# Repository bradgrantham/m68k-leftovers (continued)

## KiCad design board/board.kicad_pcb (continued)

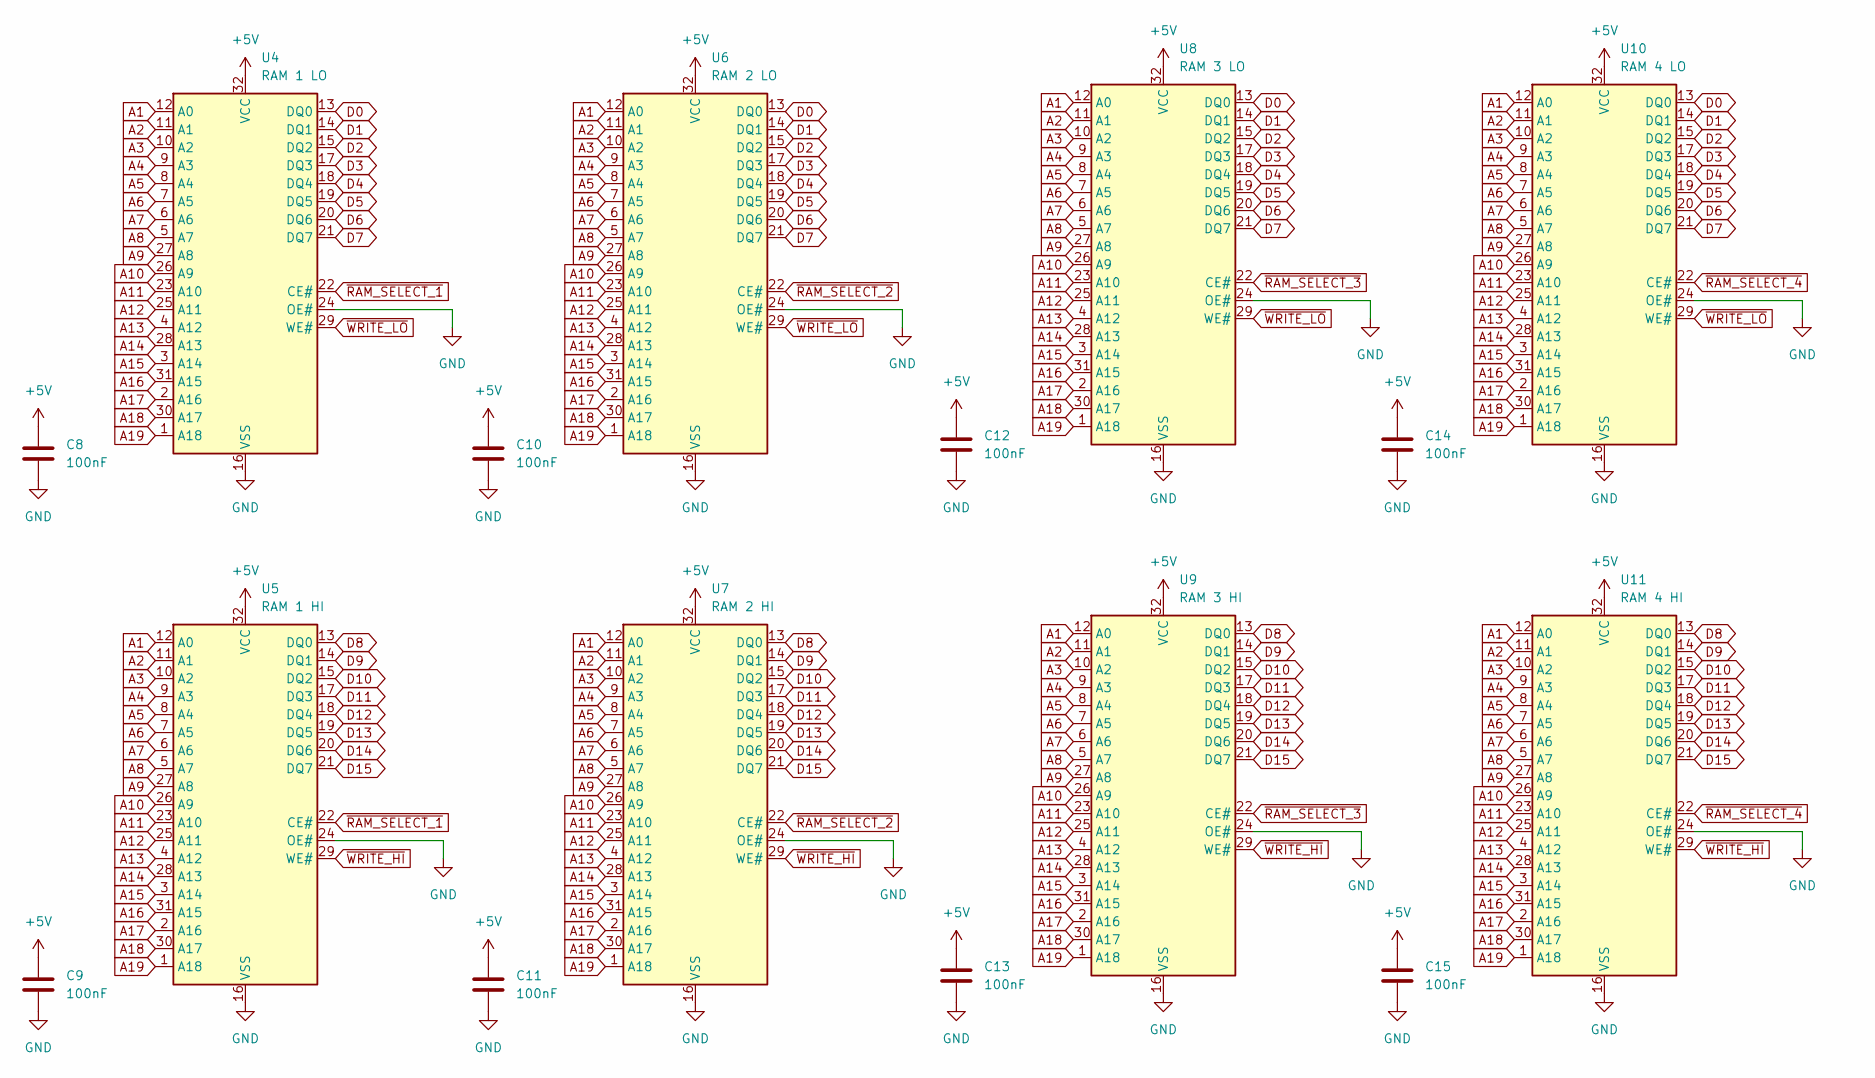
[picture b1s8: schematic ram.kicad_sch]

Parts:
C8, C9, C10, C11, C12, C13, C14, C15: 100nF; C_Disc_D5.0mm_W2.5mm_P5.00mm
U4: RAM 1 LO; DIP-32_W15.24mm
U5: RAM 1 HI; DIP-32_W15.24mm
U6: RAM 2 LO; DIP-32_W15.24mm
U7: RAM 2 HI; DIP-32_W15.24mm
U8: RAM 3 LO; DIP-32_W15.24mm
U9: RAM 3 HI; DIP-32_W15.24mm
U10: RAM 4 LO; DIP-32_W15.24mm
U11: RAM 4 HI; DIP-32_W15.24mm

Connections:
+5V: C8.1, C9.1, C10.1, C11.1, C12.1, C13.1, C14.1, C15.1, U4.32 (VCC), U5.32 (VCC), U6.32 (VCC), U7.32 (VCC), U8.32 (VCC), U9.32 (VCC), U10.32 (VCC), U11.32 (VCC); also elsewhere on the board
A1: U4.12 (A0), U5.12 (A0), U6.12 (A0), U7.12 (A0), U8.12 (A0), U9.12 (A0), U10.12 (A0), U11.12 (A0); also elsewhere on the board
A2: U4.11 (A1), U5.11 (A1), U6.11 (A1), U7.11 (A1), U8.11 (A1), U9.11 (A1), U10.11 (A1), U11.11 (A1); also elsewhere on the board
A3: U4.10 (A2), U5.10 (A2), U6.10 (A2), U7.10 (A2), U8.10 (A2), U9.10 (A2), U10.10 (A2), U11.10 (A2); also elsewhere on the board
A4: U4.9 (A3), U5.9 (A3), U6.9 (A3), U7.9 (A3), U8.9 (A3), U9.9 (A3), U10.9 (A3), U11.9 (A3); also elsewhere on the board
A5: U4.8 (A4), U5.8 (A4), U6.8 (A4), U7.8 (A4), U8.8 (A4), U9.8 (A4), U10.8 (A4), U11.8 (A4); also elsewhere on the board
A6: U4.7 (A5), U5.7 (A5), U6.7 (A5), U7.7 (A5), U8.7 (A5), U9.7 (A5), U10.7 (A5), U11.7 (A5); also elsewhere on the board
A7: U4.6 (A6), U5.6 (A6), U6.6 (A6), U7.6 (A6), U8.6 (A6), U9.6 (A6), U10.6 (A6), U11.6 (A6); also elsewhere on the board
A8: U4.5 (A7), U5.5 (A7), U6.5 (A7), U7.5 (A7), U8.5 (A7), U9.5 (A7), U10.5 (A7), U11.5 (A7); also elsewhere on the board
A9: U4.27 (A8), U5.27 (A8), U6.27 (A8), U7.27 (A8), U8.27 (A8), U9.27 (A8), U10.27 (A8), U11.27 (A8); also elsewhere on the board
A10: U4.26 (A9), U5.26 (A9), U6.26 (A9), U7.26 (A9), U8.26 (A9), U9.26 (A9), U10.26 (A9), U11.26 (A9); also elsewhere on the board
A11: U4.23 (A10), U5.23 (A10), U6.23 (A10), U7.23 (A10), U8.23 (A10), U9.23 (A10), U10.23 (A10), U11.23 (A10); also elsewhere on the board
A12: U4.25 (A11), U5.25 (A11), U6.25 (A11), U7.25 (A11), U8.25 (A11), U9.25 (A11), U10.25 (A11), U11.25 (A11); also elsewhere on the board
A13: U4.4 (A12), U5.4 (A12), U6.4 (A12), U7.4 (A12), U8.4 (A12), U9.4 (A12), U10.4 (A12), U11.4 (A12); also elsewhere on the board
A14: U4.28 (A13), U5.28 (A13), U6.28 (A13), U7.28 (A13), U8.28 (A13), U9.28 (A13), U10.28 (A13), U11.28 (A13); also elsewhere on the board
A15: U4.3 (A14), U5.3 (A14), U6.3 (A14), U7.3 (A14), U8.3 (A14), U9.3 (A14), U10.3 (A14), U11.3 (A14); also elsewhere on the board
A16: U4.31 (A15), U5.31 (A15), U6.31 (A15), U7.31 (A15), U8.31 (A15), U9.31 (A15), U10.31 (A15), U11.31 (A15); also elsewhere on the board
A17: U4.2 (A16), U5.2 (A16), U6.2 (A16), U7.2 (A16), U8.2 (A16), U9.2 (A16), U10.2 (A16), U11.2 (A16); also elsewhere on the board
A18: U4.30 (A17), U5.30 (A17), U6.30 (A17), U7.30 (A17), U8.30 (A17), U9.30 (A17), U10.30 (A17), U11.30 (A17); also elsewhere on the board
A19: U4.1 (A18), U5.1 (A18), U6.1 (A18), U7.1 (A18), U8.1 (A18), U9.1 (A18), U10.1 (A18), U11.1 (A18); also elsewhere on the board
D0: U4.13 (DQ0), U6.13 (DQ0), U8.13 (DQ0), U10.13 (DQ0); also elsewhere on the board
D1: U4.14 (DQ1), U6.14 (DQ1), U8.14 (DQ1), U10.14 (DQ1); also elsewhere on the board
D2: U4.15 (DQ2), U6.15 (DQ2), U8.15 (DQ2), U10.15 (DQ2); also elsewhere on the board
D3: U4.17 (DQ3), U6.17 (DQ3), U8.17 (DQ3), U10.17 (DQ3); also elsewhere on the board
D4: U4.18 (DQ4), U6.18 (DQ4), U8.18 (DQ4), U10.18 (DQ4); also elsewhere on the board
D5: U4.19 (DQ5), U6.19 (DQ5), U8.19 (DQ5), U10.19 (DQ5); also elsewhere on the board
D6: U4.20 (DQ6), U6.20 (DQ6), U8.20 (DQ6), U10.20 (DQ6); also elsewhere on the board
D7: U4.21 (DQ7), U6.21 (DQ7), U8.21 (DQ7), U10.21 (DQ7); also elsewhere on the board
D8: U5.13 (DQ0), U7.13 (DQ0), U9.13 (DQ0), U11.13 (DQ0); also elsewhere on the board
D9: U5.14 (DQ1), U7.14 (DQ1), U9.14 (DQ1), U11.14 (DQ1); also elsewhere on the board
D10: U5.15 (DQ2), U7.15 (DQ2), U9.15 (DQ2), U11.15 (DQ2); also elsewhere on the board
D11: U5.17 (DQ3), U7.17 (DQ3), U9.17 (DQ3), U11.17 (DQ3); also elsewhere on the board
D12: U5.18 (DQ4), U7.18 (DQ4), U9.18 (DQ4), U11.18 (DQ4); also elsewhere on the board
D13: U5.19 (DQ5), U7.19 (DQ5), U9.19 (DQ5), U11.19 (DQ5); also elsewhere on the board
D14: U5.20 (DQ6), U7.20 (DQ6), U9.20 (DQ6), U11.20 (DQ6); also elsewhere on the board
D15: U5.21 (DQ7), U7.21 (DQ7), U9.21 (DQ7), U11.21 (DQ7); also elsewhere on the board
GND: C8.2, C9.2, C10.2, C11.2, C12.2, C13.2, C14.2, C15.2, U4.16 (VSS), U4.24 (OE#), U5.16 (VSS), U5.24 (OE#), U6.16 (VSS), U6.24 (OE#), U7.16 (VSS), U7.24 (OE#), U8.16 (VSS), U8.24 (OE#), U9.16 (VSS), U9.24 (OE#), U10.16 (VSS), U10.24 (OE#), U11.16 (VSS), U11.24 (OE#); also elsewhere on the board
~RAM_SELECT_1: U4.22 (CE#), U5.22 (CE#); also elsewhere on the board
~RAM_SELECT_2: U6.22 (CE#), U7.22 (CE#); also elsewhere on the board
~RAM_SELECT_3: U8.22 (CE#), U9.22 (CE#); also elsewhere on the board
~RAM_SELECT_4: U10.22 (CE#), U11.22 (CE#); also elsewhere on the board
~WRITE_HI: U5.29 (WE#), U7.29 (WE#), U9.29 (WE#), U11.29 (WE#); also elsewhere on the board
~WRITE_LO: U4.29 (WE#), U6.29 (WE#), U8.29 (WE#), U10.29 (WE#); also elsewhere on the board

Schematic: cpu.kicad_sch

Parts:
C4, C5: 100nF; C_Disc_D5.0mm_W2.5mm_P5.00mm
R3, R4, R6: 100K; R_Axial_DIN0207_L6.3mm_D2.5mm_P10.16mm_Horizontal
R13, R34, R54, R55: 10K; R_Axial_DIN0207_L6.3mm_D2.5mm_P10.16mm_Horizontal
U1: MC68000P; DIP-64_W22.86mm

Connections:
+5V: C4.1, C5.1, R3.1, R4.1, R6.1, R13.1, R34.1, R54.1, R55.1, U1.14 (V_{CC}), U1.49 (V_{CC}); also elsewhere on the board
A1: U1.29 (A1); also elsewhere on the board
A2: U1.30 (A2); also elsewhere on the board
A3: U1.31 (A3); also elsewhere on the board
A4: U1.32 (A4); also elsewhere on the board
A5: U1.33 (A5); also elsewhere on the board
A6: U1.34 (A6); also elsewhere on the board
A7: U1.35 (A7); also elsewhere on the board
A8: U1.36 (A8); also elsewhere on the board
A9: U1.37 (A9); also elsewhere on the board
A10: U1.38 (A10); also elsewhere on the board
A11: U1.39 (A11); also elsewhere on the board
A12: U1.40 (A12); also elsewhere on the board
A13: U1.41 (A13); also elsewhere on the board
A14: U1.42 (A14); also elsewhere on the board
A15: U1.43 (A15); also elsewhere on the board
A16: U1.44 (A16); also elsewhere on the board
A17: U1.45 (A17); also elsewhere on the board
A18: U1.46 (A18); also elsewhere on the board
A19: U1.47 (A19); also elsewhere on the board
A20: U1.48 (A20); also elsewhere on the board
A21: U1.50 (A21); also elsewhere on the board
A22: U1.51 (A22); also elsewhere on the board
A23: U1.52 (A23); also elsewhere on the board
CPUCLK: U1.15 (CLK); also elsewhere on the board
D0: U1.5 (D0); also elsewhere on the board
D1: U1.4 (D1); also elsewhere on the board
D2: U1.3 (D2); also elsewhere on the board
D3: U1.2 (D3); also elsewhere on the board
D4: U1.1 (D4); also elsewhere on the board
D5: U1.64 (D5); also elsewhere on the board
D6: U1.63 (D6); also elsewhere on the board
D7: U1.62 (D7); also elsewhere on the board
D8: U1.61 (D8); also elsewhere on the board
D9: U1.60 (D9); also elsewhere on the board
D10: U1.59 (D10); also elsewhere on the board
D11: U1.58 (D11); also elsewhere on the board
D12: U1.57 (D12); also elsewhere on the board
D13: U1.56 (D13); also elsewhere on the board
D14: U1.55 (D14); also elsewhere on the board
D15: U1.54 (D15); also elsewhere on the board
FC0: U1.28 (FC0); also elsewhere on the board
FC1: U1.27 (FC1); also elsewhere on the board
FC2: U1.26 (FC2); also elsewhere on the board
GND: C4.2, C5.2, U1.16 (GND), U1.53 (GND); also elsewhere on the board
unnamed: R6.2, U1.21 (~VPA)
R/~W: U1.9 (R/~W); also elsewhere on the board
~AS: U1.6 (~AS); also elsewhere on the board
~BERR: U1.22 (~BERR); also elsewhere on the board
~BGACK: R4.2, U1.12 (~BGACK); also elsewhere on the board
~BG: U1.11 (~BG); also elsewhere on the board
~BR: R3.2, U1.13 (~BR); also elsewhere on the board
~DTACK: U1.10 (~DTACK); also elsewhere on the board
~HALT: R54.2, U1.17 (~HALT); also elsewhere on the board
~IPL0: R13.2, U1.25 (~IPL0); also elsewhere on the board
~IPL1: R34.2, U1.24 (~IPL1); also elsewhere on the board
~IPL2: R55.2, U1.23 (~IPL2); also elsewhere on the board
~LDS: U1.8 (~LDS); also elsewhere on the board
~RESET: U1.18 (~RESET); also elsewhere on the board
~UDS: U1.7 (~UDS); also elsewhere on the board

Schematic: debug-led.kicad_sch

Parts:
C24, C36: 100nF; C_Disc_D5.0mm_W2.5mm_P5.00mm
C25: 10nF; C_Disc_D3.0mm_W1.6mm_P2.50mm
C26: 100µF; CP_Radial_D5.0mm_P2.50mm
J7: STEREO_OUT; SAMESKY_SJ3-35063B; PARTREV 1.0
LS1: Speaker; MagneticBuzzer_StarMicronics_QMX
R52, R53: 1K; R_Axial_DIN0207_L6.3mm_D2.5mm_P10.16mm_Horizontal
R57, R58: 100; R_Axial_DIN0207_L6.3mm_D2.5mm_P10.16mm_Horizontal
R59: 47; R_Axial_DIN0207_L6.3mm_D2.5mm_P10.16mm_Horizontal
R60: 4610X-R2R-103LF; BO_4610X
U15: LM358; DIP-8_W7.62mm
U23: 74HC373; DIP-20_W7.62mm

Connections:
+5V: C24.1, C36.1, U15.8 (V+), U23.20 (VCC); also elsewhere on the board
AUDIO0: R60.9, U23.2 (O0)
AUDIO1: R60.8, U23.5 (O1)
AUDIO2: R60.7, U23.6 (O2)
AUDIO3: R60.6, U23.9 (O3)
AUDIO4: R60.5, U23.12 (O4)
AUDIO5: R60.4, U23.15 (O5)
AUDIO6: R60.3, U23.16 (O6)
AUDIO7: R60.2, U23.19 (O7)
AUDIO_LE: U23.11 (LE); also elsewhere on the board
D0: U23.3 (D0); also elsewhere on the board
D1: U23.4 (D1); also elsewhere on the board
D2: U23.7 (D2); also elsewhere on the board
D3: U23.8 (D3); also elsewhere on the board
D4: U23.13 (D4); also elsewhere on the board
D5: U23.14 (D5); also elsewhere on the board
D6: U23.17 (D6); also elsewhere on the board
D7: U23.18 (D7); also elsewhere on the board
GND: C24.2, C25.2, C36.2, J7.1, LS1.2, R53.1, R60.10, U15.4 (V-), U15.5 (+), U23.1 (OE), U23.10 (GND); also elsewhere on the board
unnamed: C25.1, C26.1, R52.2
unnamed: C26.2, R53.2, R57.2, R58.2
unnamed: J7.2, R57.1
unnamed: J7.3, R58.1
unnamed: J7.4, R59.2
unnamed: LS1.1, R59.1
unnamed: R60.1, U15.3 (+)
unnamed: R52.1, U15.1, U15.2 (-)
unnamed: U15.6 (-), U15.7

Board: 4 copper layers, 117 parts (0 on the bottom side), 147 nets, no tracks yet.

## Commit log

2026-01-13 initial commit of PCB, unfinished
2026-01-28 fill out most functionality - passes ERC
2026-01-28 straggler
2026-01-28 change IO to 8051 variant, add audio
2026-01-30 design draft complete, added footprints
2026-01-30 ignore fp-info-cache
2026-01-31 start of PCB and MMU
2026-02-04 checkpoint
2026-02-04 project library symbols
2026-02-06 checkpoint - maybe unfinishable
2026-02-07 checkpoint before reordering 1508 inputs
2026-02-07 checkpoint before CPST shrink
2026-02-09 checkpoint before deleting composite video
2026-02-09 checkpoint before compact flash
2026-02-10 CF card, composite, VGA
2026-02-14 add test points
2026-02-17 Board rev1 PCB complete, already have a spot fix
2026-02-19 better organize firmware files
2026-02-19 notes exported from Google Doc
